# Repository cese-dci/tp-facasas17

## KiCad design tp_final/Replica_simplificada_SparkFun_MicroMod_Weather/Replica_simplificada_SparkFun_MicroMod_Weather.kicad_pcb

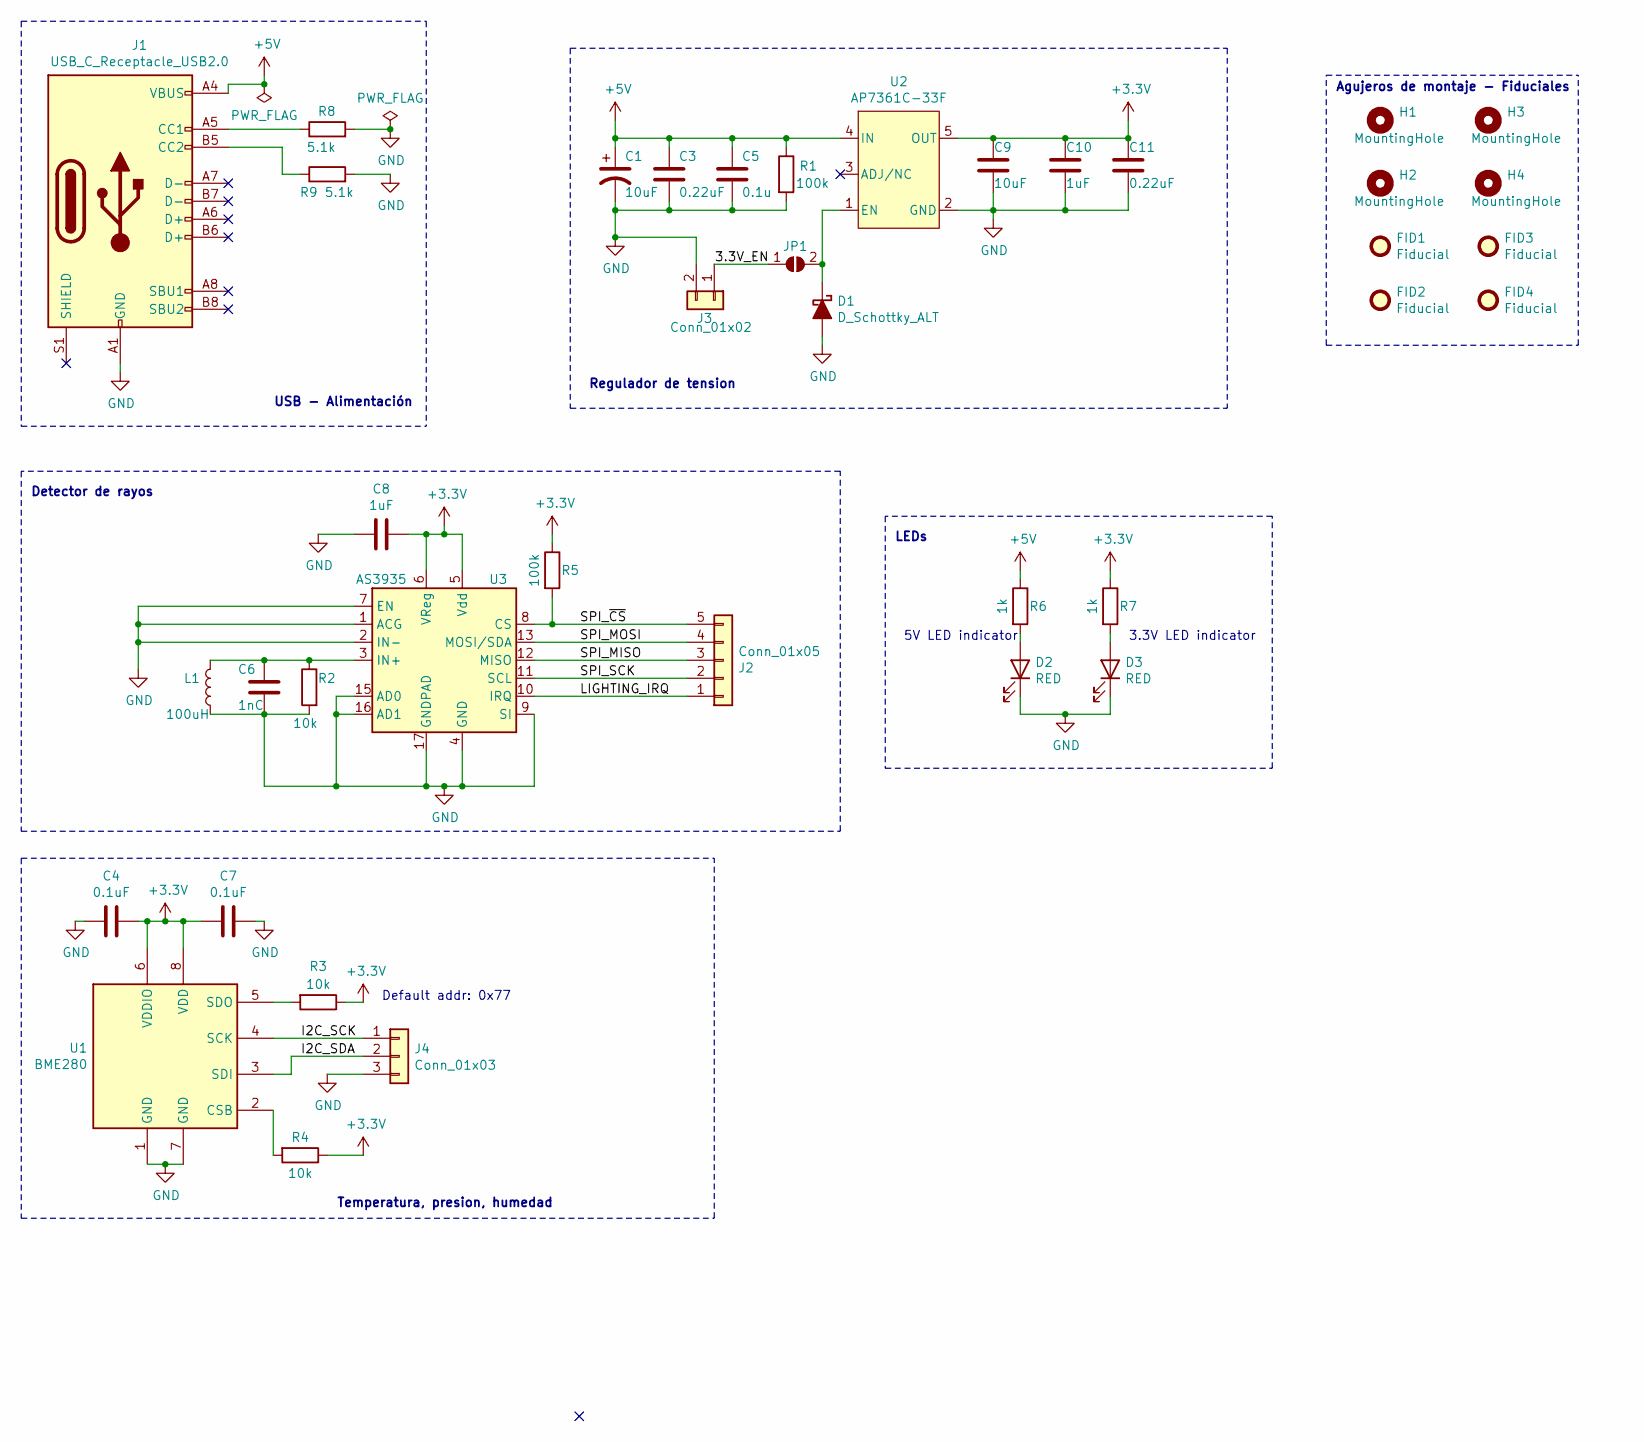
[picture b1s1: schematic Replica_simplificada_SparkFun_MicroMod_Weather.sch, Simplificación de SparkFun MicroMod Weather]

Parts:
C1: 10uF; CP_Elec_4x3
C3, C11: 0.22uF; C_1206_3216Metric
C4, C7: 0.1uF; C_1206_3216Metric
C5: 0.1u; C_1206_3216Metric
C6: 1nC; C_1206_3216Metric
C8, C10: 1uF; C_1206_3216Metric
C9: 10uF; C_1206_3216Metric
D1: D_Schottky_ALT; D_SOD-123F
D2, D3: RED; LED_1206_3216Metric
FID1, FID2, FID3, FID4: Fiducial; Fiducial_0.5mm_Mask1.5mm
H1, H2, H3, H4: MountingHole; MountingHole_2.2mm_M2_ISO7380
J1: USB_C_Receptacle_USB2.0; USB_C_Receptacle_XKB_U262-16XN-4BVC11
J2: Conn_01x05; PinSocket_1x05_P2.54mm_Vertical
J3: Conn_01x02; PinSocket_1x02_P2.54mm_Vertical
J4: Conn_01x03; PinSocket_1x03_P2.54mm_Vertical
JP1: SolderJumper_2_Open; SolderJumper-2_P1.3mm_Open_Pad1.0x1.5mm
L1: 100uH; L_1812_4532Metric
R1, R5: 100k; R_1206_3216Metric
R2, R3, R4: 10k; R_1206_3216Metric
R6, R7: 1k; R_1206_3216Metric
R8, R9: 5.1k; R_1206_3216Metric
U1: BME280; Bosch_LGA-8_2.5x2.5mm_P0.65mm_ClockwisePinNumbering
U2: AP7361C-33F; SOT-89-5
U3: AS3935; MLPQ-16-1EP_4x4mm_P0.65mm_EP2.8x2.8mm

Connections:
+3V3: C4.1, C7.2, C8.2, C9.1, C10.1, C11.1, R3.1, R4.1, R5.1, R7.1, U1.6 (VDDIO), U1.8 (VDD), U2.5 (OUT), U3.5 (Vdd), U3.6 (VReg)
+5V: C1.1, C3.1, C5.1, J1.A4 (VBUS), J1.A9 (VBUS), J1.B4 (VBUS), J1.B9 (VBUS), R1.1, R6.1, U2.4 (IN)
/3.3V_EN: J3.1, JP1.1 (A)
/I2C_SCK: J4.1, U1.4 (SCK)
/I2C_SDA: J4.2, U1.3 (SDI)
/LIGHTING_IRQ: J2.1, U3.10 (IRQ)
/SPI_MISO: J2.3, U3.12 (MISO)
/SPI_MOSI: J2.4, U3.13 (MOSI/SDA)
/SPI_SCK: J2.2, U3.11 (SCL)
/SPI_~CS~: J2.5, R5.2, U3.8 (CS)
GND: C1.2, C3.2, C4.2, C5.2, C6.2, C7.1, C8.1, C9.2, C10.2, C11.2, D1.2 (A), D2.1 (K), D3.1 (K), J1.A1 (GND), J1.A12 (GND), J1.B1 (GND), J1.B12 (GND), J3.2, J4.3, L1.2, R1.2, R2.2, R8.2, R9.2, U1.1 (GND), U1.7 (GND), U2.2 (GND), U3.1 (ACG), U3.2 (IN-), U3.4 (GND), U3.7 (EN), U3.9 (SI), U3.15 (AD0), U3.16 (AD1), U3.17 (GNDPAD)
unnamed: C6.1, L1.1, R2.1, U3.3 (IN+)
unnamed: D1.1 (K), JP1.2 (B), U2.1 (EN)
unnamed: D2.2 (A), R6.2
unnamed: D3.2 (A), R7.2
unnamed: J1.A5 (CC1), R8.1
unnamed: J1.B5 (CC2), R9.1
unnamed: R3.2, U1.5 (SDO)
unnamed: R4.2, U1.2 (CSB)

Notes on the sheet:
Regulador de tension
Detector de rayos
USB - Alimentación
3.3V LED indicator
5V LED indicator
LEDs
Default addr: 0x77
Temperatura, presion, humedad
Agujeros de montaje - Fiduciales

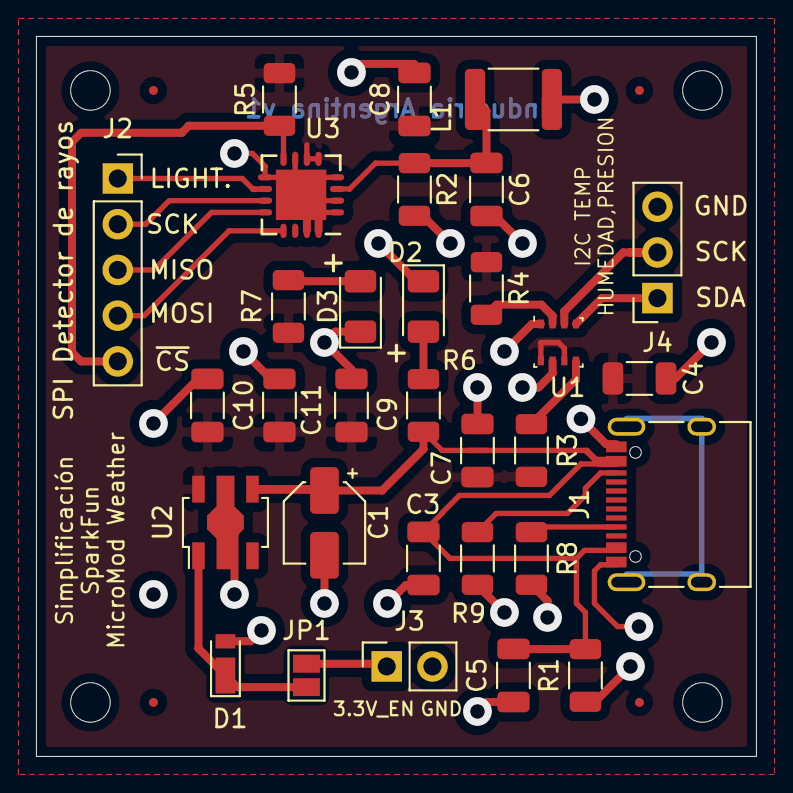
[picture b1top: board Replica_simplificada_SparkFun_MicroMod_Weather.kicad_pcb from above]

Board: 2 copper layers, 40.0 x 40.0 mm, 39 parts (0 on the bottom side), 19 nets.

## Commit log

2021-03-29 Esquematico revision 1
2021-03-30 PCB revision 1 listo
2021-04-01 Primeras correciones
2021-04-02 Mejoro posicionamiento
2021-04-09 Agrego mounting hole y fiduciales al esquematico
2021-04-17 Correciones finales

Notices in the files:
tp_final/Replica_simplificada_SparkFun_MicroMod_Weather/Replica_simplificada_SparkFun_MicroMod_Weather.kicad_pcb:
Released under the Creative Commons Attribution Share-Alike 4.0 Licence
tp_final/Replica_simplificada_SparkFun_MicroMod_Weather/Replica_simplificada_SparkFun_MicroMod_Weather.sch:
https://creativecommons.org/license/by-sa/4.0
